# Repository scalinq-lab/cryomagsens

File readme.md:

*(Poster from presentation at SQA conference 2026)*

# Cryomagsens

## Project History
This repository is [SCALINQ AB's](https://www.scalinq.com/) continuation of a project that originally began as a Bachelor's Thesis project at the 
 [Department of Microtechnology and Nanoscience at Chalmers University of Technology](https://www.chalmers.se/en/departments/mc2/), 
 in collaboration with SCALINQ AB.

The original proof-of-concept repository can be referenced for historical context [here](
https://github.com/cryomagsens/cryomagsens)

## Description
Cryomagsens is a magnetic field sensor, developed specifically for cryogenic applications. It features a custom sensor 
built around the AKM HQ0811 InAs Hall effect sensor with an integrated temperature sensor and a custom signal processing
unit (SPU), using phase sensitive detection to extract the signal. The signal processing unit is built around the 
Raspberry Pi Pico 2W microcontroller development board, and features hardware support for measurements with 3 different 
sensor units at once.

The system also includes a custom built brass Helmholtz coil for controlled calibration in a cryogenic environment.

All PCB design files for the signal processing unit can be found in `/signal_processing_unit_pcb`, 
and all the PCB design files for the sensor unit can be found in `/sensor_unit_pcb`.

All the mechanical files for the Helmholtz coil and custom PCB mounts can be found in `/mechanical_designs`.

The signal processing unit firmware can be found in `/signal_processing_unit_firmware` and the calibration and test
scripts can be found in `/calibration_scripts`.

## Results
Experimental results show a sensitivity of 0.39 V/T at 5.2 K and 300 µA drive current, with a 20 % relative error at 1 µT.

## Known issues
During work with the project, we have encountered the following problems:

* When running the calibration system at low temperatures, significant self heating occurs. The sensor itself has a low thermal load for currents up to 3 mA through the hall sensor, but thermalizes badly through the brass Helmholtz coil.
* After spinning current demodulation, a significant DC component remains to the signal, corresponding to ~10 µT of signal strenght.
* Uncertain temperature calibration, as mounting point for external temperature sensor is far from the integrated sensor.
* Possible self-induced magnetic fields on the sensor PCB due to signal path asymmetry.

The following is a list of non implemented features.
* No check for current source saturation (even though the signal processing unit has hardware support for such a check)
* No way to load calibration data to the SPU. Right now the SPU returns a voltage instead of a magnetic flux density.
* PCB design mistakes (fixed in the PCB design files but visible in the pictures).

The following is a list of proposed changes:
* Implement way to disable/enable current sources to the Hall element and diode independently without interfering with the ADC.
* Invert the connector signals (J1 - J3 on the signal processing unit PCB - Would make the cables bidirectional even when GND and PRS lines aren't shielded).
* Protect the sensitive signals between ground layers during the full signal path.   

## Licensing
This repository contains both software and hardware design files, licensed separately:

- All software (located in `/signal_processing_unit_firmware` and `/calibration_scripts`) is licensed under the MIT License. See [LICENSE-MIT](LICENSE-MIT).

- All hardware design files (PCB Schematics, Layouts, 3D CAD models, etc.) (located in `/mechanical_designs`, `/sensor_unit_pcb`, and `/signal_processing_unit_pcb`) are licensed under the CERN Open Hardware Licence Version 2 - Permissive. See [LICENSE-CERN-OHL-P](LICENSE-CERN-OHL-P).

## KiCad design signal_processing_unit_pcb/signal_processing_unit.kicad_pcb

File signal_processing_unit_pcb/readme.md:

# Signal Processing Unit: Schematics and PCB Design

*(Assembled signal processing unit)*

## Design

The signal processing unit *(SPU)* was designed in KiCad 10 and manufactured by JLCPCB. It is based around the Raspberry Pi Pico 2W development board and features hardware support for simultaneous magnetic field measurements from three separate cryomagsens sensor units. 

The SPU supports both USB and WiFi interfacing and is physically grounded to the chassis to minimize noise. Custom 3D models for components outside of the standard KiCad libraries were sourced from the SamacSys Library Loader.

## Cabling

The board features three 10-pin Molex PicoBlade connectors. These route to external 15-pin D-sub connectors on the enclosure to ensure a secure physical connection.

## Known Issues 

There are three known design mistakes on the physical PCB shown above. **Note:** All three issues have been corrected in the provided KiCad schematic and PCB design files.

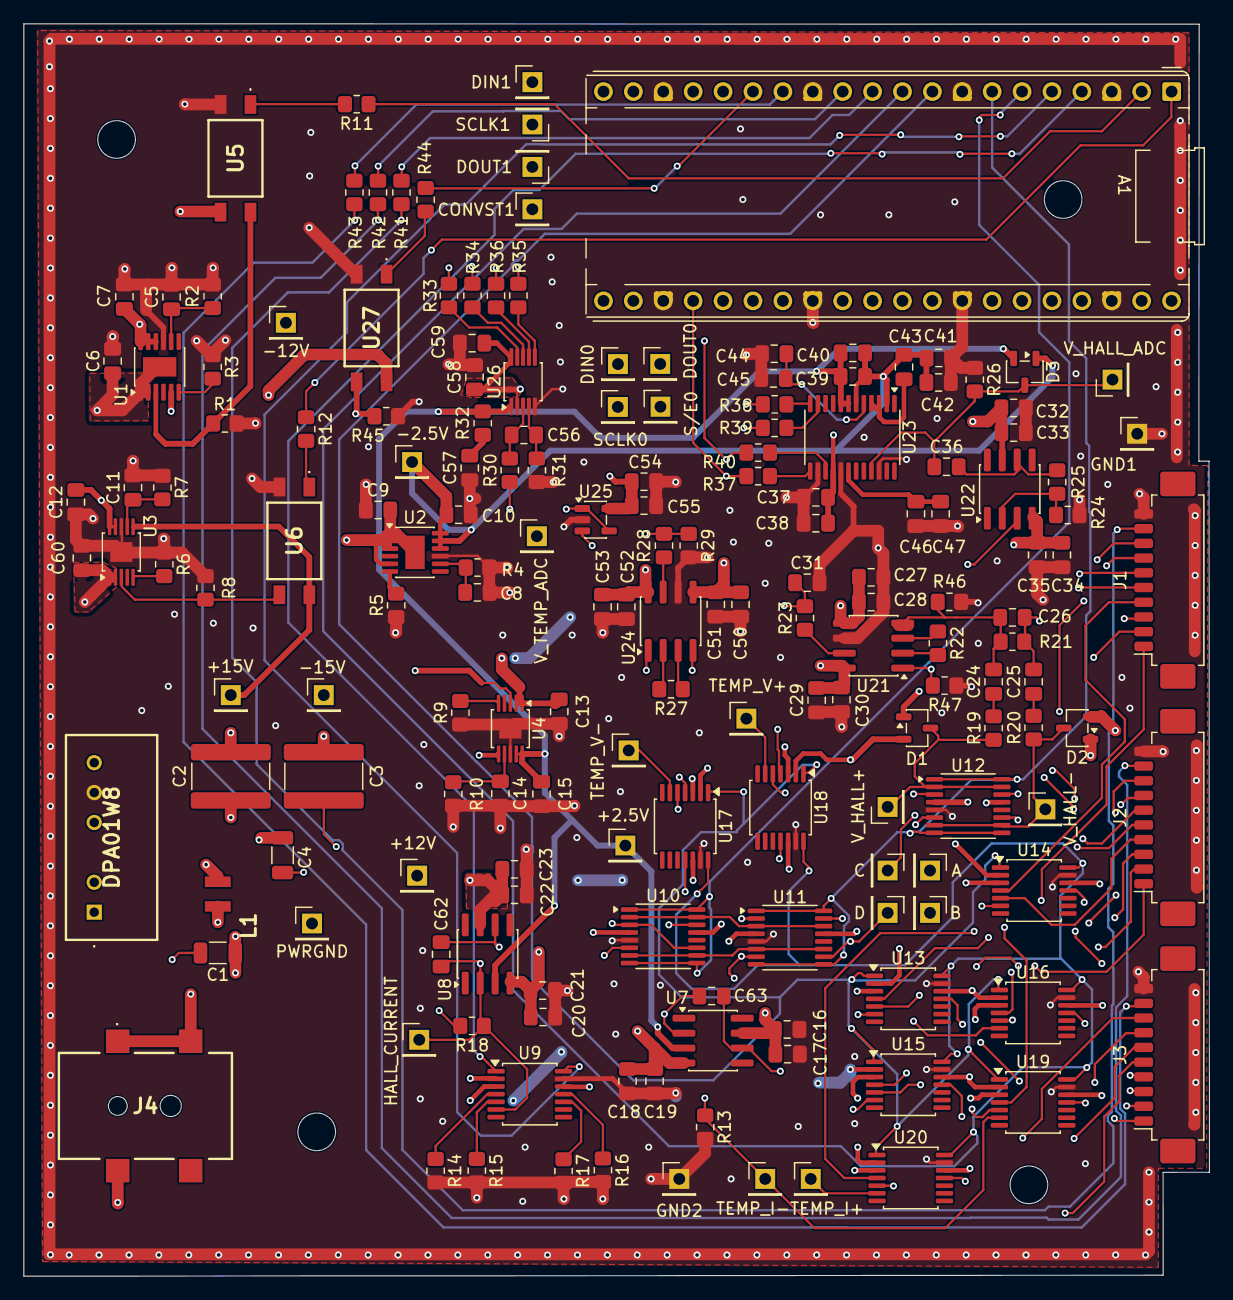
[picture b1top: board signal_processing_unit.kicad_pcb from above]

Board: 6 copper layers, 100.7 x 106.4 mm, 178 parts (0 on the bottom side), 121 nets.

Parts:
+2.5: +2.5V; PinHeader_1x01_P2.54mm_Vertical
+12: +12V; PinHeader_1x01_P2.54mm_Vertical
+15: +15V; PinHeader_1x01_P2.54mm_Vertical
-2.5: -2.5V; PinHeader_1x01_P2.54mm_Vertical
-12: -12V; PinHeader_1x01_P2.54mm_Vertical
-15: -15V; PinHeader_1x01_P2.54mm_Vertical
A1: RaspberryPi_Pico; Raspberry_Pi_Pico_mod
A2: A; PinHeader_1x01_P2.54mm_Vertical
B1: B; PinHeader_1x01_P2.54mm_Vertical
C1, C4: 2.2uF/100V; C_1206_3216Metric
C2, C3: 1,5nF/5KV; C_1825_4564Metric
C5, C8, C12, C13, C15, C60: 4,7uF; C_0805_2012Metric_Pad1.18x1.45mm_HandSolder
C6, C7, C9, C10, C16, C18, C20, C23, C27, C29, C32, C35, C38, C40, C41, C50, C53, C54, C57: 10µF; C_0805_2012Metric_Pad1.18x1.45mm_HandSolder
C11, C14: 470n; C_0805_2012Metric_Pad1.18x1.45mm_HandSolder
C17, C19, C21, C22, C28, C30, C33, C34, C37, C39, C42, C44, C46, C51, C52, C55: 100nF; C_0805_2012Metric_Pad1.18x1.45mm_HandSolder
C24, C25: 10nF; C_0805_2012Metric_Pad1.18x1.45mm_HandSolder
C26: 47nF; C_0805_2012Metric_Pad1.18x1.45mm_HandSolder
C31, C56: 10n; C_0805_2012Metric_Pad1.18x1.45mm_HandSolder
C36: 47n; C_0805_2012Metric_Pad1.18x1.45mm_HandSolder
C43: 4.7µF; C_0805_2012Metric_Pad1.18x1.45mm_HandSolder
C45, C47, C58, C59: 1µF; C_0805_2012Metric_Pad1.18x1.45mm_HandSolder
C61: C; PinHeader_1x01_P2.54mm_Vertical
C62, C63: 22pF; C_0805_2012Metric_Pad1.18x1.45mm_HandSolder
CONVST1: CONVST1; PinHeader_1x01_P2.54mm_Vertical
D1, D2, D3: BAV199-7-F; SOT-23-3
D4: D; PinHeader_1x01_P2.54mm_Vertical
DIN0: DIN0; PinHeader_1x01_P2.54mm_Vertical
DIN1: DIN1; PinHeader_1x01_P2.54mm_Vertical
DOUT0: DOUT0; PinHeader_1x01_P2.54mm_Vertical
DOUT1: DOUT1; PinHeader_1x01_P2.54mm_Vertical
DPA01W8: DPA01W815
GND1: GND1; PinHeader_1x01_P2.54mm_Vertical
GND2: GND2; PinHeader_1x01_P2.54mm_Vertical
H1, H2, H3, H4: MountingHole; MountingHole_3.2mm_M3
HALL_CURR1: HALL_CURRENT; PinHeader_1x01_P2.54mm_Vertical
J1, J2, J3: Conn_01x10_Pin; Molex_PicoBlade_53261-1071_1x10-1MP_P1.25mm_Horizontal
J4: 54-00164; DC_plug
L1: WE-RFH_1008A; WE-RFH68
PWRGND1: PWRGND; PinHeader_1x01_P2.54mm_Vertical
R1, R8, R45: 100 K; R_0805_2012Metric_Pad1.20x1.40mm_HandSolder
R2, R7: 120k; R_0805_2012Metric_Pad1.20x1.40mm_HandSolder
R3, R5: 7.5k; R_0805_2012Metric_Pad1.20x1.40mm_HandSolder
R4, R10: 25 K; R_0805_2012Metric_Pad1.20x1.40mm_HandSolder
R6, R9: 499; R_0805_2012Metric_Pad1.20x1.40mm_HandSolder
R11, R12, R44: 330; R_0805_2012Metric_Pad1.20x1.40mm_HandSolder
R13: 250k; R_0805_2012Metric_Pad1.20x1.40mm_HandSolder
R14: 820; R_0805_2012Metric_Pad1.20x1.40mm_HandSolder
R15: 8.2k; R_0805_2012Metric_Pad1.20x1.40mm_HandSolder
R16: 82k; R_0805_2012Metric_Pad1.20x1.40mm_HandSolder
R17: 300; R_0805_2012Metric_Pad1.20x1.40mm_HandSolder
R18: 0; R_0805_2012Metric_Pad1.20x1.40mm_HandSolder
R19, R20, R23: 470; R_0805_2012Metric_Pad1.20x1.40mm_HandSolder
R21: 3.3k; R_0805_2012Metric_Pad1.20x1.40mm_HandSolder
R22: 100; R_0805_2012Metric_Pad1.20x1.40mm_HandSolder
R24, R41, R42, R43: 1k; R_0805_2012Metric_Pad1.20x1.40mm_HandSolder
R25, R28, R29, R46, R47: 10k; R_0805_2012Metric_Pad1.20x1.40mm_HandSolder
R26: 1.6k; R_0805_2012Metric_Pad1.20x1.40mm_HandSolder
R27: 1M; R_0805_2012Metric_Pad1.20x1.40mm_HandSolder
R30, R31: 10; R_0805_2012Metric_Pad1.20x1.40mm_HandSolder
R32: 0.47; R_0805_2012Metric_Pad1.20x1.40mm_HandSolder
R33, R34, R35, R36, R37, R38, R39, R40: 47; R_0805_2012Metric_Pad1.20x1.40mm_HandSolder
S/E0: S/E0; PinHeader_1x01_P2.54mm_Vertical
SCLK0: SCLK0; PinHeader_1x01_P2.54mm_Vertical
SCLK1: SCLK1; PinHeader_1x01_P2.54mm_Vertical
TEMP_I+1: TEMP_I+; PinHeader_1x01_P2.54mm_Vertical
TEMP_I-1: TEMP_I-; PinHeader_1x01_P2.54mm_Vertical
TEMP_V+1: TEMP_V+; PinHeader_1x01_P2.54mm_Vertical
TEMP_V-1: TEMP_V-; PinHeader_1x01_P2.54mm_Vertical
U1, U2: LT3094xMSE; MSOP-12-1EP_3x4.039mm_P0.65mm_EP1.651x2.845mm
U3, U4: LT3042xMSE; MSOP-10-1EP_3x3mm_P0.5mm_EP1.68x1.88mm
U5, U6, U27: APC817D1SL
U7, U8, U22: AD8675ARZ; SOIC-8_3.9x4.9mm_P1.27mm
U9, U13, U14, U15, U16, U17, U18, U19, U20: ADG1404; TSSOP-14_4.4x5mm_P0.65mm
U10, U11, U12: ADG1413; TSSOP-16_4.4x5mm_P0.65mm
U21, U24: AD8421ARZ; SOIC-8_3.9x4.9mm_P1.27mm
U23: AD7175-2BRUZ; TSSOP-24_4.4x7.8mm_P0.65mm
U25: AD8603; TSOT-23-5
U26: ADS8866; MSOP-10_3x3mm_P0.5mm
V_HALL+1: V_HALL+; PinHeader_1x01_P2.54mm_Vertical
V_HALL-1: V_HALL-; PinHeader_1x01_P2.54mm_Vertical
V_HALL_ADC1: V_HALL_ADC; PinHeader_1x01_P2.54mm_Vertical
V_TEMP_ADC1: V_TEMP_ADC; PinHeader_1x01_P2.54mm_Vertical

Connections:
15V: C1.1, J4.A1, J4.A2, L1.1
+2.5V: +2.5.1 (1_1), C15.2, C39.2, C40.2, D3.2 (K2), R32.1, U4.9 (OUTS), U4.10 (OUT), U7.3 (+), U8.3 (+), U23.7 (AVDD1), U23.8 (AVDD2), U26.1 (REF)
+3.3V: A1.36 (3V3), C37.1, C38.1, C54.1, C55.2, C58.2, C59.1, U23.16 (IOVDD), U25.5 (V+), U26.2 (AVDD), U26.10 (DVDD)
+12V: +12.1 (1_1), C12.2, C13.2, C16.2, C17.2, C22.2, C23.2, C29.2, C30.2, C32.2, C33.2, C52.2, C53.2, D1.2 (K2), D2.2 (K2), U3.9 (OUTS), U3.10 (OUT), U4.1 (IN), U4.2 (IN), U4.6 (PGFB), U7.7 (V+), U8.7 (V+), U9.2 (EN), U9.12 (VDD), U10.13 (VDD), U11.13 (VDD), U12.13 (VDD), U13.2 (EN), U13.12 (VDD), U14.2 (EN), U14.12 (VDD), U15.2 (EN), U15.12 (VDD), U16.2 (EN), U16.12 (VDD), U17.2 (EN), U17.12 (VDD), U18.2 (EN), U18.12 (VDD), U19.2 (EN), U19.12 (VDD), U20.2 (EN), U20.12 (VDD), U21.8 (Vs+), U22.7 (V+), U24.8 (Vs+), U27.4 (CLCTR)
+15V: +15.1 (1_1), C2.2, C60.2, DPA01W8.4 (Vout+), U3.1 (IN), U3.2 (IN), U3.6 (PGFB), U6.4 (CLCTR)
-2.5V: -2.5.1 (1_1), C10.2, C39.1, C40.1, C41.1, C42.1, C43.2, D3.1 (A1), U2.10 (OUTS), U2.11 (OUT), U2.12 (OUT), U23.2 (REF-), U23.6 (AVSS)
-12V: -12.1 (1_1), C7.2, C9.2, C18.2, C19.2, C20.2, C21.2, C27.2, C28.2, C34.2, C35.2, C50.2, C51.2, D1.1 (A1), D2.1 (A1), U1.10 (OUTS), U1.11 (OUT), U1.12 (OUT), U2.1 (IN), U2.2 (IN), U2.3 (EN/UV), U2.5 (PGFB), U2.13 (IN), U7.4 (V-), U8.4 (V-), U9.3 (Vss), U10.4 (VSS), U11.4 (VSS), U12.4 (VSS), U13.3 (Vss), U14.3 (Vss), U15.3 (Vss), U16.3 (Vss), U17.3 (Vss), U18.3 (Vss), U19.3 (Vss), U20.3 (Vss), U21.5 (Vs-), U22.4 (V-), U24.5 (Vs-)
-15V: -15.1 (1_1), C3.2, C6.2, DPA01W8.6 (Vout-), U1.1 (IN), U1.2 (IN), U1.5 (PGFB), U1.13 (IN), U5.3 (EMTR)
/2.5V_CTRL: A1.15 (GPIO11), R44.2
/CONN0: A1.9 (GPIO6), U13.1 (A0), U14.1 (A0), U15.1 (A0), U16.1 (A0), U17.1 (A0), U18.1 (A0), U19.1 (A0), U20.1 (A0)
/CONN1: A1.10 (GPIO7), U13.14 (A1), U14.14 (A1), U15.14 (A1), U16.14 (A1), U17.14 (A1), U18.14 (A1), U19.14 (A1), U20.14 (A1)
/CURR_CTRL0: A1.4 (GPIO2), U9.1 (A0)
/CURR_CTRL1: A1.5 (GPIO3), U9.14 (A1)
/HALL_CTRL0: A1.6 (GPIO4), U10.1 (IN1), U10.8 (IN4), U10.9 (IN3), U10.16 (IN2)
/HALL_CTRL1: A1.7 (GPIO5), U11.1 (IN1), U11.8 (IN4), U11.9 (IN3), U11.16 (IN2), U12.1 (IN1), U12.8 (IN4), U12.9 (IN3), U12.16 (IN2)
/Hall_voltage: C36.2, D3.3 (K1/A2), R26.2, U23.21 (AIN0), V_HALL_ADC1.1 (1_1)
/I+: C63.1, TEMP_I+1.1 (1_1), U7.6 (OUT), U20.6 (D)
/I+0: J1.8, U20.4 (S1)
/I+1: J2.8, U20.5 (S2)
/I+2: J3.8, U20.11 (S3)
/I-: C63.2, R13.1, TEMP_I-1.1 (1_1), U7.2 (-), U19.6 (D)
/I-0: J1.7, U19.4 (S1)
/I-1: J2.7, U19.5 (S2)
/I-2: J3.7, U19.11 (S3)
/LINREGG_ON0: A1.1 (GPIO0), R12.1
/LINREGG_ON1: A1.2 (GPIO1), R11.1
/PICO_ADC_0: A1.31 (GPIO26_ADC0), R18.2
/PRES0: J1.9, R41.1
/PRES1: J2.9, R42.1
/PRES2: J3.9, R43.1
/SPI0_*SYNC/*ERROR: A1.22 (GPIO17), R40.1, S/E0.1 (1_1)
/SPI0_DIN: A1.25 (GPIO19), DIN0.1 (1_1), R38.1
/SPI0_DOUT: A1.21 (GPIO16), DOUT0.1 (1_1), R39.1
/SPI0_SCLK: A1.24 (GPIO18), R37.1, SCLK0.1 (1_1)
/SPI1_CONVST: A1.17 (GPIO13), CONVST1.1 (1_1), R35.1
/SPI1_DIN: A1.20 (GPIO15), DIN1.1 (1_1), R33.1
/SPI1_DOUT: A1.16 (GPIO12), DOUT1.1 (1_1), R36.1
/SPI1_SCLK: A1.19 (GPIO14), R34.1, SCLK1.1 (1_1)
/V+: TEMP_V+1.1 (1_1), U18.6 (D), U24.4 (+)
/V+0: J1.6, U18.4 (S1)
/V+1: J2.6, U18.5 (S2)
/V+2: J3.6, U18.11 (S3)
/V-: TEMP_V-1.1 (1_1), U17.6 (D), U24.1 (-)
/V-0: J1.5, U17.4 (S1)
/V-1: J2.5, U17.5 (S2)
/V-2: J3.5, U17.11 (S3)
/a: A2.1 (1_1), U11.2 (D1), U12.14 (S2), U13.6 (D)
/a0: J1.1, U13.4 (S1)
/a1: J2.1, U13.5 (S2)
/a2: J3.1, U13.11 (S3)
/b: B1.1 (1_1), U11.15 (D2), U12.3 (S1), U14.6 (D)
/b0: J1.4, U14.4 (S1)
/b1: J2.4, U14.5 (S2)
/b2: J3.4, U14.11 (S3)
/c: C61.1 (1_1), U11.7 (D4), U12.11 (S3), U15.6 (D)
/c0: J1.2, U15.4 (S1)
/c1: J2.2, U15.5 (S2)
/c2: J3.2, U15.11 (S3)
/d: D4.1 (1_1), U11.10 (D3), U12.6 (S4), U16.6 (D)
/d0: J1.3, U16.4 (S1)
/d1: J2.3, U16.5 (S2)
/d2: J3.3, U16.11 (S3)
GND: A1.3 (GND), A1.8 (GND), A1.13 (GND), A1.18 (GND), A1.23 (GND), A1.28 (GND), A1.33 (AGND), A1.38 (GND), C5.2, C6.1, C7.1, C8.2, C9.1, C10.1, C11.2, C12.1, C13.1, C14.2, C15.1, C16.1, C17.1, C18.1, C19.1, C20.1, C21.1, C22.1, C23.1, C27.1, C28.1, C29.1, C30.1, C31.2, C32.1, C33.1, C34.1, C35.1, C37.2, C38.2, C41.2, C42.2, C44.1, C45.1, C46.1, C47.1, C50.1, C51.1, C52.1, C53.1, C54.2, C55.1, C57.1, C58.1, C59.2, C60.1, DPA01W8.5 (Com_(gnd)), GND1.1 (1_1), GND2.1 (1_1), J1.10, J2.10, J3.10, R1.2, R2.1, R3.1, R4.1, R5.1, R6.1, R7.1, R8.2, R9.1, R10.1, R13.2, R14.2, R15.2, R16.2, R17.2, R24.1, R26.1, R29.2, R31.1, R45.2, R46.1, R47.2, U1.9 (GND), U2.9 (GND), U3.8 (GND), U3.11 (GND), U4.8 (GND), U4.11 (GND), U5.2 (CATHODE), U6.2 (CATHODE), U9.13 (GND), U10.5 (GND), U11.5 (GND), U12.5 (GND), U13.13 (GND), U14.13 (GND), U15.13 (GND), U16.13 (GND), U17.13 (GND), U18.13 (GND), U19.13 (GND), U20.13 (GND), U21.6 (Ref), U23.14 (*CS), U23.17 (DGND), U23.22 (AIN1), U24.6 (Ref), U25.2 (V-), U26.5 (GND), U27.2 (CATHODE)
GNDPWR: C1.2, C3.1, C4.2, DPA01W8.1 (Vin-), J4.B1, PWRGND1.1 (1_1)
unnamed: A1.11 (GPIO8), R41.2
unnamed: A1.12 (GPIO9), R42.2
unnamed: A1.14 (GPIO10), R43.2
unnamed: C24.1, R19.2
unnamed: C25.1, R20.2
unnamed: C57.2, R32.2
unnamed: D1.3 (K1/A2), R19.1, U12.2 (D1), U12.15 (D2), V_HALL+1.1 (1_1)
unnamed: D2.3 (K1/A2), R20.1, U12.7 (D4), U12.10 (D3), V_HALL-1.1 (1_1)
unnamed: C2.1, C4.1, DPA01W8.2 (Vin+), L1.2
unnamed: R22.1, U21.3 (Rg)
unnamed: R22.2, U21.2 (Rg)
unnamed: R23.1, U21.7
unnamed: R27.1, U24.3 (Rg)
unnamed: R27.2, U24.2 (Rg)
unnamed: R28.1, U24.7
unnamed: R1.1, U1.3 (EN/UV), U5.4 (CLCTR)
unnamed: R3.2, U1.6 (ILIM)
unnamed: C5.1, R2.2, U1.8 (SET)
unnamed: R5.2, U2.6 (ILIM)
unnamed: C8.1, R4.2, U2.8 (SET)
unnamed: R8.1, U3.3 (EN/UV), U6.3 (EMTR)
unnamed: R6.2, U3.5 (ILIM)
unnamed: C11.1, R7.2, U3.7 (SET)
unnamed: R9.2, U4.5 (ILIM)
unnamed: C14.1, R10.2, U4.7 (SET)
unnamed: R11.2, U5.1 (ANODE)
unnamed: R12.2, U6.1 (ANODE)
unnamed: R14.1, U9.4 (S1)
unnamed: R15.1, U9.5 (S2)
unnamed: R16.1, U9.11 (S3)
unnamed: R17.1, U9.10 (S4)
unnamed: U10.2 (D1), U10.15 (D2), U11.3 (S1), U11.14 (S2)
unnamed: U10.7 (D4), U10.10 (D3), U11.6 (S4), U11.11 (S3)
unnamed: C62.1, U8.6 (OUT), U10.3 (S1), U10.11 (S3)
unnamed: C62.2, HALL_CURR1.1 (1_1), R18.1, U8.2 (-), U9.6 (D), U10.6 (S4), U10.14 (S2)
unnamed: C24.2, C26.1, R21.2, R46.2, U21.4 (+)
unnamed: C25.2, C26.2, R21.1, R47.1, U21.1 (-)
unnamed: C31.1, R23.2, U22.3 (+)
unnamed: R24.2, R25.1, U22.2 (-)
unnamed: C36.1, R25.2, U22.6 (OUT)
unnamed: R40.2, U23.15 (*SYNC/*ERROR)
unnamed: R38.2, U23.12 (DIN)
unnamed: R39.2, U23.11 (DOUT/*RDY)
unnamed: C43.1, U23.3 (REF+), U23.4 (REFOUT)
unnamed: C44.2, C45.2, U23.5 (REGCAPA)
unnamed: C46.2, C47.2, U23.18 (REGCAPD)
unnamed: R37.2, U23.13 (SCLK)
unnamed: R28.2, R29.1, U25.3 (+)
unnamed: R30.1, U25.1, U25.4 (-), V_TEMP_ADC1.1 (1_1)
unnamed: C56.1, R30.2, U26.3 (AIN+)
unnamed: C56.2, R31.2, U26.4 (AIN-)
unnamed: R35.2, U26.6 (CONVST)
unnamed: R33.2, U26.9 (DIN)
unnamed: R36.2, U26.7 (DOUT)
unnamed: R34.2, U26.8 (SCLK)
unnamed: R44.1, U27.1 (ANODE)
unnamed: R45.1, U4.3 (EN/UV), U27.3 (EMTR)

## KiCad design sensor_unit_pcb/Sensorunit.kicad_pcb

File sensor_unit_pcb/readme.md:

# Sensor unit: Schematics and PCB Design

*(Sensor unit)*

## Design

The sensor unit was designed in KiCad 10 and manufactured by JLCPCB. It is built in a flex PCB material to achieve 
a very small build height, in order to come very close to the device under test. The Flex PCB is mounted to a copper 
spine (see `..\mechanical_designs` for the full design) for thermalisation purposes. The total build height of the sensor unit is 1.1 mm.

The sensor unit features a AKM HQ0811 InAs Hall element as a magnetic field sensor, a 1N4148 Si diode as a temperature sensor and a 10-pin Molex PicoBlade connector for a good and stable connection.

## Working principle

### Hall sensor
The Hall element has four nodes, here denoted *a, b, c, d*. When a current is pushed fron *a* to *c*, a potential difference can be measured between *b* and *d*, which scales linearly with the applied orthogonal magnetic flux density.
When a current is pushed from *b* to *d*, a similar potential difference can be measured between *a* and *c*.
By modulating the current directiion and through which axis the current is pushed, the remaining DC offset due to asymmetries in the element can be eliminated.

### Diode temperature sensor
The sensor unit also features a 4-wire measurement setup for the diode, which acts as a temperature sensor.
The nominal drive current of the diode is 10 µA.

### Presence pin.
The sensor unit features a presence pin *(denoted PRS)*, which is internally connected to the ground pin on the sensor PCB.
When connected to the signal processing unit, a GPIO pin is pulled low through the sensor unit, indicating that 
a sensor is connected and allowing current output.

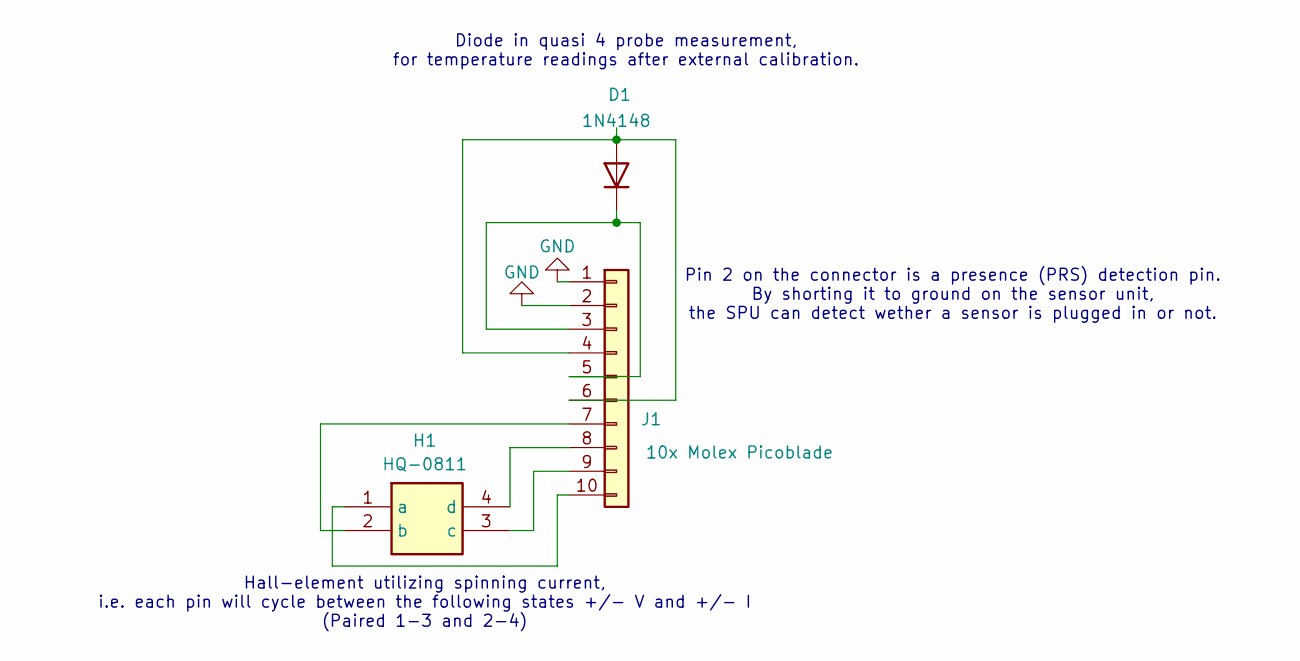
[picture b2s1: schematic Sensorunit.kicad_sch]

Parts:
D1: 1N4148; D_SOD-882
H1: HQ-0811; HQ0811; Manufacturer_Part_Number HQ-0811
J1: 10x Molex Picoblade; Molex_PicoBlade_53261-1071_1x10-1MP_P1.25mm_Horizontal

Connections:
GND: J1.1, J1.2
unnamed: D1.2 (A), J1.4, J1.6
unnamed: D1.1 (K), J1.3, J1.5
unnamed: H1.1 (a), J1.10
unnamed: H1.2 (b), J1.7
unnamed: H1.3 (c), J1.9
unnamed: H1.4 (d), J1.8

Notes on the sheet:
Hall-element utilizing spinning current, i.e. each pin will cycle between the following states +/- V and +/- I (Paired 1-3 and 2-4)
Pin 2 on the connector is a presence (PRS) detection pin. By shorting it to ground on the sensor unit, the SPU can detect wether a sensor is plugged in or not.
Diode in quasi 4 probe measurement, for temperature readings after external calibration.

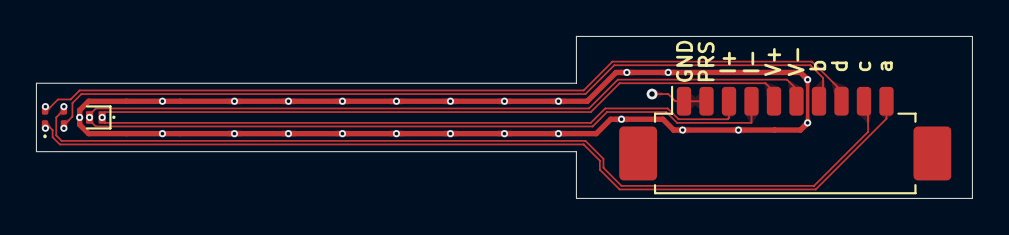
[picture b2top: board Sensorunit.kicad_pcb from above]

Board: 2 copper layers, 52.0 x 9.0 mm, 3 parts (0 on the bottom side), 7 nets.
